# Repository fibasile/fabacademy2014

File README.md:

# FabAcademy 2014 website

In order to be able to build the site or serve it dynamically you will need the following:

- Node.js 10.0.*
- harp.js

You can grab node.js from the [nodejs.org](http://nodejs.org) website, and install a binary package for your platform.

Once this is done just type:

	> npm install -g harp

Then clone this repository and run:

	> harp server

this will start a webserver on your localhost:9000 port with the complete website.

If you want a static version, you can run in the same folder:

	> harp compile

This will create a www folder containing the static website.

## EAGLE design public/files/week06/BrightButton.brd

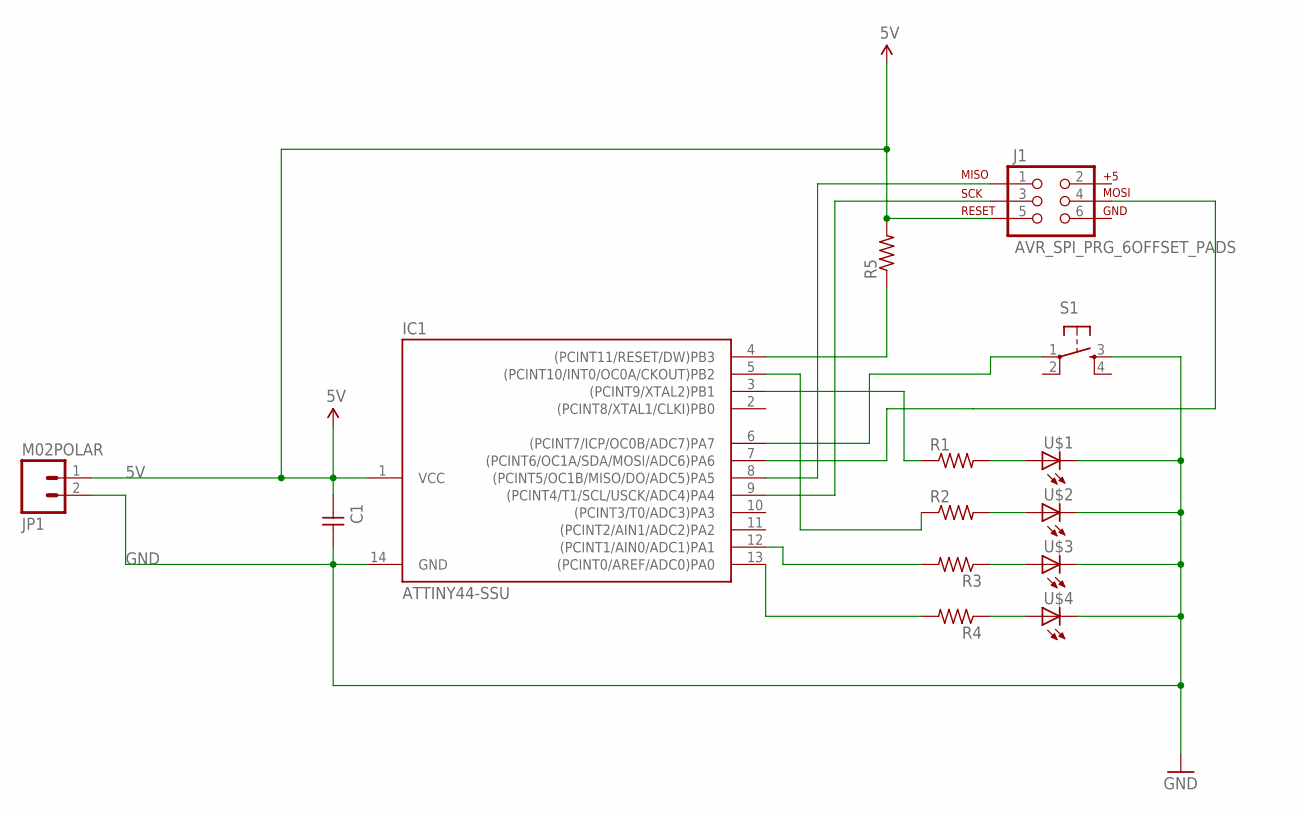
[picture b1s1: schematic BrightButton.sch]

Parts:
C1: UNPOLARIZED_CAPACITOR1206; 1206
IC1: ATTINY44-SSU; SOIC14
J1: AVR_SPI_PRG_6OFFSET_PADS; 2X3_OFFSET
JP1: M02POLAR; MOLEX-1X2
R1, R2, R3, R4, R5: RESISTOR1206; 1206
S1: 6MM_SWITCH6MM_SWITCH; 6MM_SWITCH
U$1, U$2, U$3, U$4: LED1206; 1206

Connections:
5V: C1.1, IC1.1 (VCC), J1.5, JP1.1, R5.2
GND: C1.2, IC1.14 (GND), JP1.2, S1.3 (S), U$1.2 (C), U$2.2 (C), U$3.2 (C), U$4.2 (C)
unnamed: R3.1, U$3.1 (A)
unnamed: IC1.12 ((PCINT1/AIN0/ADC1)PA1), R3.2
unnamed: R2.2, U$2.1 (A)
unnamed: R4.1, U$4.1 (A)
unnamed: R1.2, U$1.1 (A)
unnamed: IC1.5 ((PCINT10/INT0/OC0A/CKOUT)PB2), R2.1
unnamed: IC1.3 ((PCINT9/XTAL2)PB1), R1.1
unnamed: IC1.13 ((PCINT0/AREF/ADC0)PA0), R4.2
unnamed: IC1.4 ((PCINT11/RESET/DW)PB3), R5.1
unnamed: IC1.8 ((PCINT5/OC1B/MISO/DO/ADC5)PA5), J1.1
unnamed: IC1.9 ((PCINT4/T1/SCL/USCK/ADC4)PA4), J1.3
unnamed: IC1.7 ((PCINT6/OC1A/SDA/MOSI/ADC6)PA6), J1.4
unnamed: IC1.6 ((PCINT7/ICP/OC0B/ADC7)PA7), S1.1

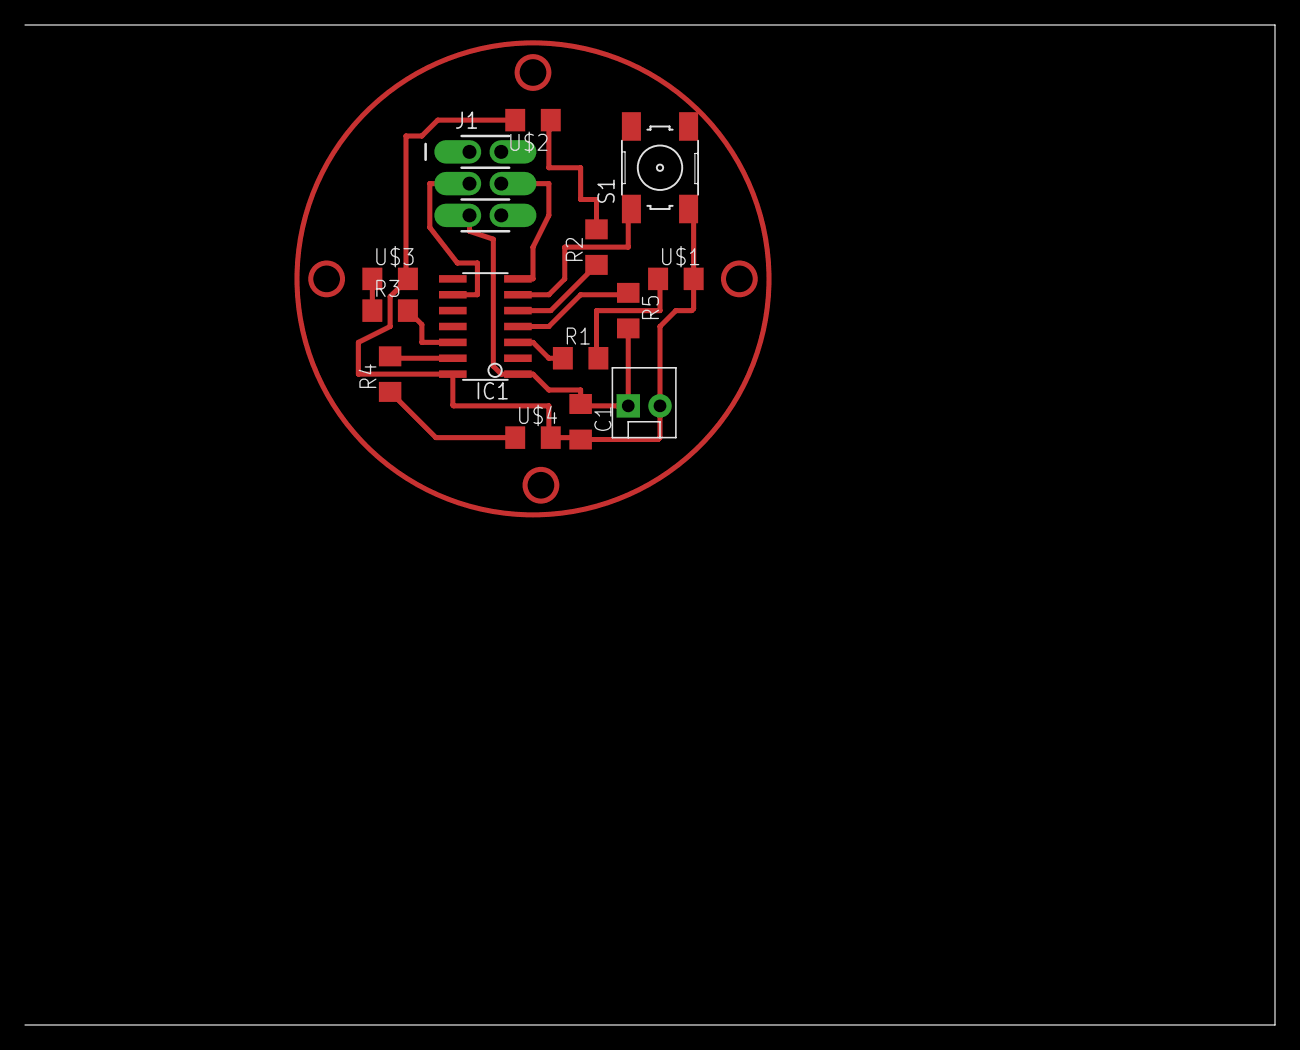
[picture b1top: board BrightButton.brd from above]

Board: 2 copper layers, 100.0 x 80.0 mm, 14 parts (0 on the bottom side), 15 nets.

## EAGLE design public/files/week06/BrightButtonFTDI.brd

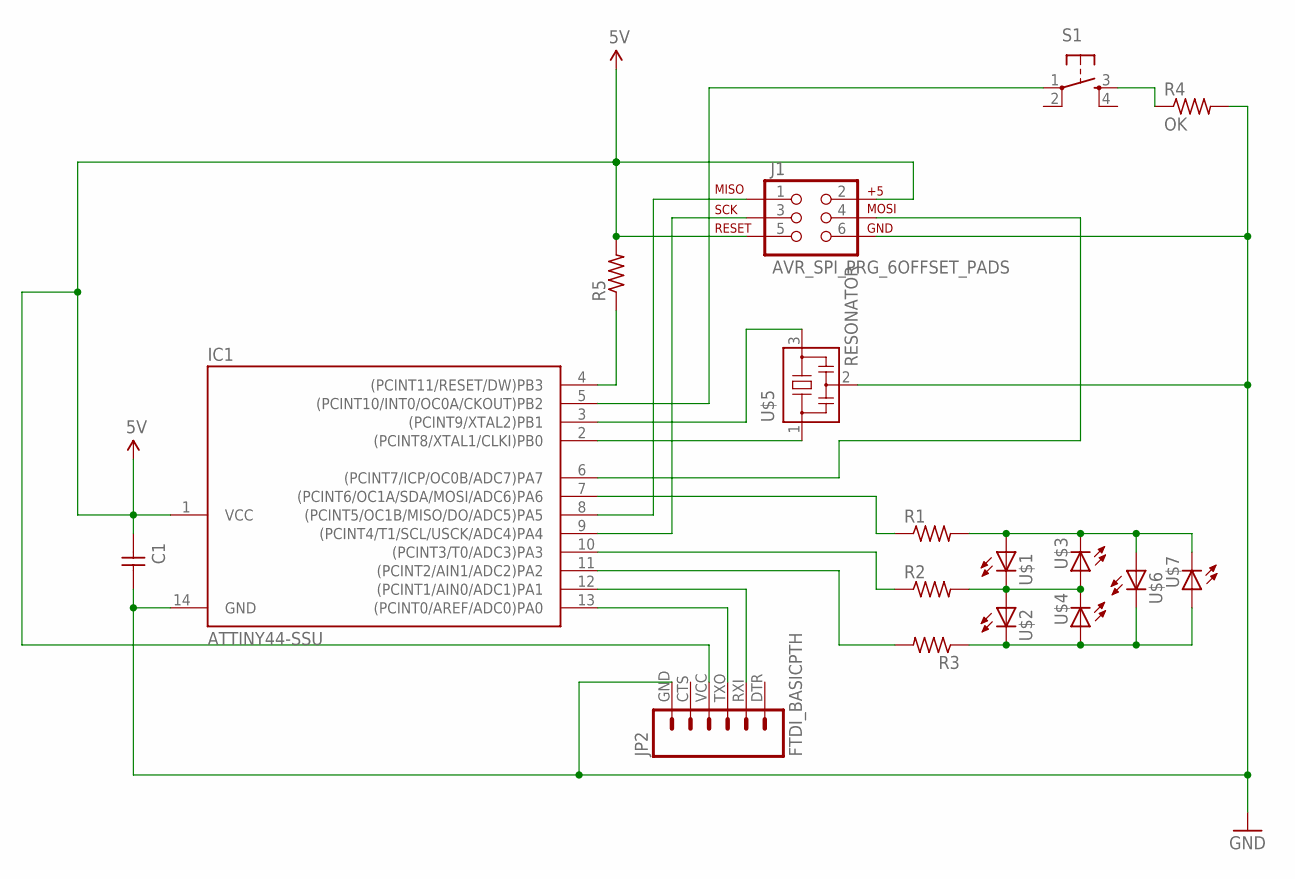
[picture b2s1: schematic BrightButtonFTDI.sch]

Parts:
C1: UNPOLARIZED_CAPACITOR1206; 1206
IC1: ATTINY44-SSU; SOIC14
J1: AVR_SPI_PRG_6OFFSET_PADS; 2X3_OFFSET
JP2: FTDI_BASICPTH; FTDI_BASIC
R1, R2, R3, R5: RESISTOR1206; 1206
R4: OK; 1206
S1: 6MM_SWITCH6MM_SWITCH; 6MM_SWITCH
U$1, U$2, U$3, U$4, U$6, U$7: LED1206; 1206
U$5: RESONATOR; EFOBM

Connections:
5V: C1.1, IC1.1 (VCC), J1.2, J1.5, JP2.VCC (4), R5.2
GND: C1.2, IC1.14 (GND), JP2.GND (6), R4.2, U$5.2
unnamed: R2.2, U$1.2 (C), U$2.1 (A), U$3.1 (A), U$4.2 (C)
unnamed: IC1.13 ((PCINT0/AREF/ADC0)PA0), JP2.TXO (3)
unnamed: R1.2, U$1.1 (A), U$3.2 (C), U$6.1 (A), U$7.2 (C)
unnamed: R3.1, U$2.2 (C), U$4.1 (A), U$6.2 (C), U$7.1 (A)
unnamed: R4.1, S1.3 (S)
unnamed: IC1.12 ((PCINT1/AIN0/ADC1)PA1), JP2.RXI (2)
unnamed: IC1.2 ((PCINT8/XTAL1/CLKI)PB0), U$5.1
unnamed: IC1.3 ((PCINT9/XTAL2)PB1), U$5.3
unnamed: IC1.4 ((PCINT11/RESET/DW)PB3), R5.1
unnamed: IC1.8 ((PCINT5/OC1B/MISO/DO/ADC5)PA5), J1.1
unnamed: IC1.9 ((PCINT4/T1/SCL/USCK/ADC4)PA4), J1.3
unnamed: IC1.6 ((PCINT7/ICP/OC0B/ADC7)PA7), J1.4
unnamed: IC1.5 ((PCINT10/INT0/OC0A/CKOUT)PB2), S1.1
unnamed: IC1.7 ((PCINT6/OC1A/SDA/MOSI/ADC6)PA6), R1.1
unnamed: IC1.10 ((PCINT3/T0/ADC3)PA3), R2.1
unnamed: IC1.11 ((PCINT2/AIN1/ADC2)PA2), R3.2

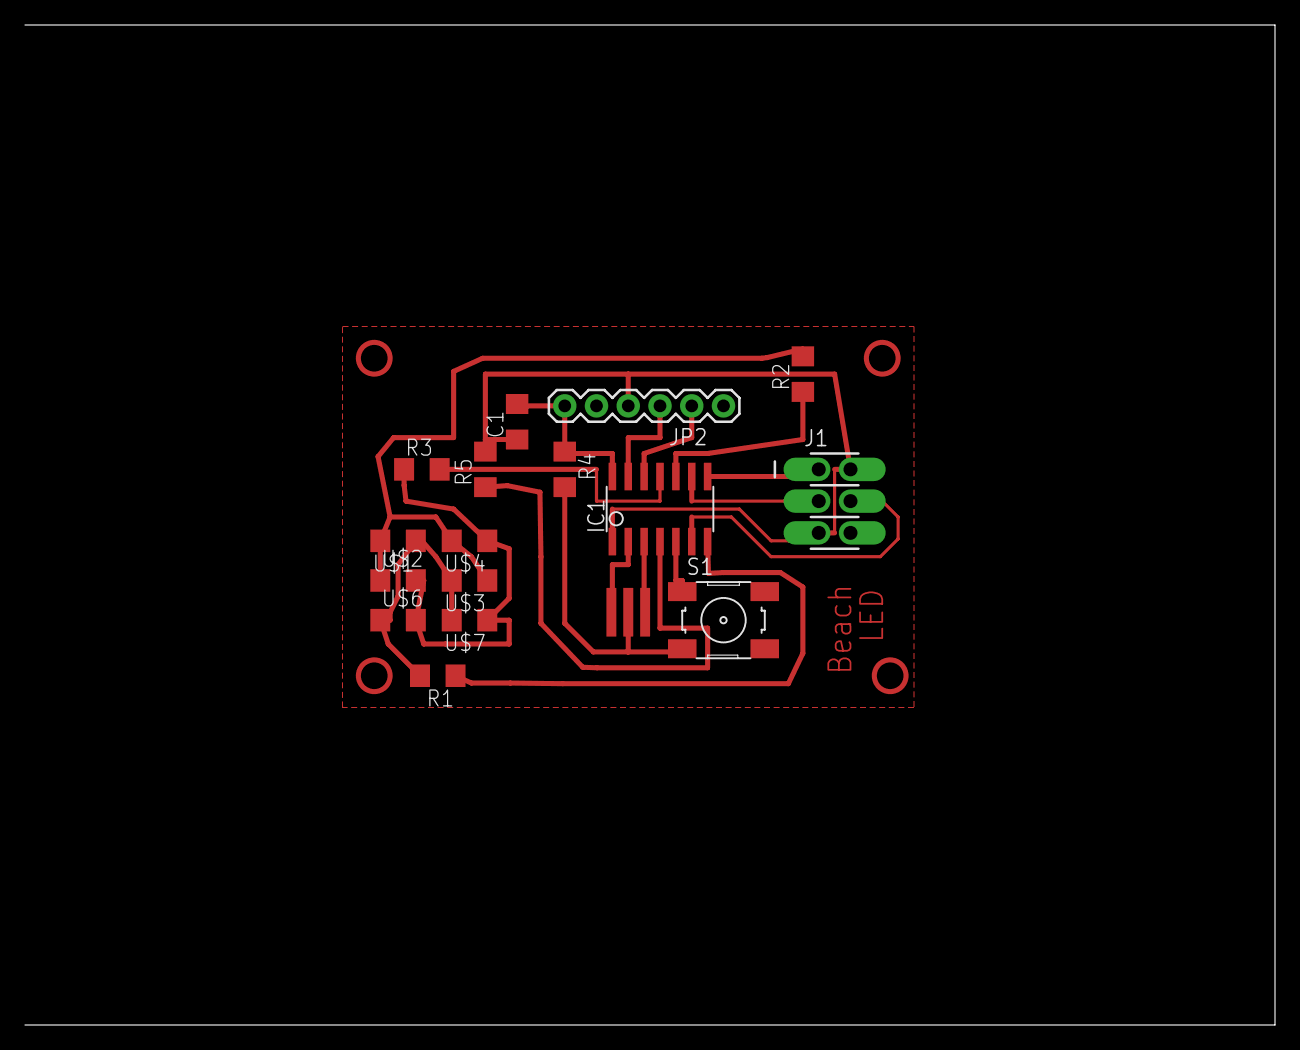
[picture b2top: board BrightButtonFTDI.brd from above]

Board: 2 copper layers, 100.0 x 80.0 mm, 17 parts (0 on the bottom side), 18 nets.

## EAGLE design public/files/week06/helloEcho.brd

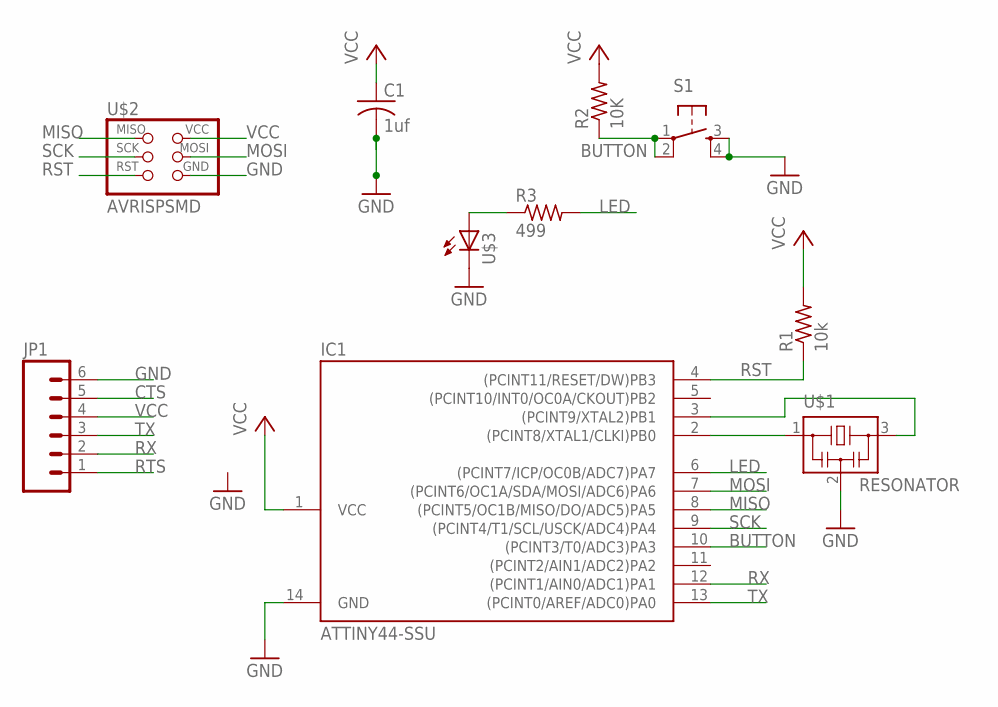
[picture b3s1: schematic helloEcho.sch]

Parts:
C1: 1uf; C1206
IC1: ATTINY44-SSU; SOIC14
JP1: M06SMD; 1X06-SMD
R1: 10k; R1206
R2: 10K; 1206
R3: 499; 1206
S1: 6MM_SWITCH6MM_SWITCH; 6MM_SWITCH
U$1: RESONATOR; EFOBM
U$2: AVRISPSMD; 2X03SMD
U$3: LED1206; 1206

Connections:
BUTTON: IC1.10 ((PCINT3/T0/ADC3)PA3), R2.1, S1.1, S1.2 (P1)
CTS: JP1.5
GND: C1.2, IC1.14 (GND), JP1.6, S1.3 (S), S1.4 (S1), U$1.2, U$2.6 (GND), U$3.2 (C)
LED: IC1.6 ((PCINT7/ICP/OC0B/ADC7)PA7), R3.2
MISO: IC1.8 ((PCINT5/OC1B/MISO/DO/ADC5)PA5), U$2.1 (MISO)
MOSI: IC1.7 ((PCINT6/OC1A/SDA/MOSI/ADC6)PA6), U$2.4 (MOSI)
unnamed: IC1.2 ((PCINT8/XTAL1/CLKI)PB0), U$1.1
unnamed: IC1.3 ((PCINT9/XTAL2)PB1), U$1.3
unnamed: R3.1, U$3.1 (A)
RST: IC1.4 ((PCINT11/RESET/DW)PB3), R1.1, U$2.5 (RST)
RTS: JP1.1
RX: IC1.12 ((PCINT1/AIN0/ADC1)PA1), JP1.2
SCK: IC1.9 ((PCINT4/T1/SCL/USCK/ADC4)PA4), U$2.3 (SCK)
TX: IC1.13 ((PCINT0/AREF/ADC0)PA0), JP1.3
VCC: C1.1, IC1.1 (VCC), JP1.4, R1.2, R2.2, U$2.2 (VCC)

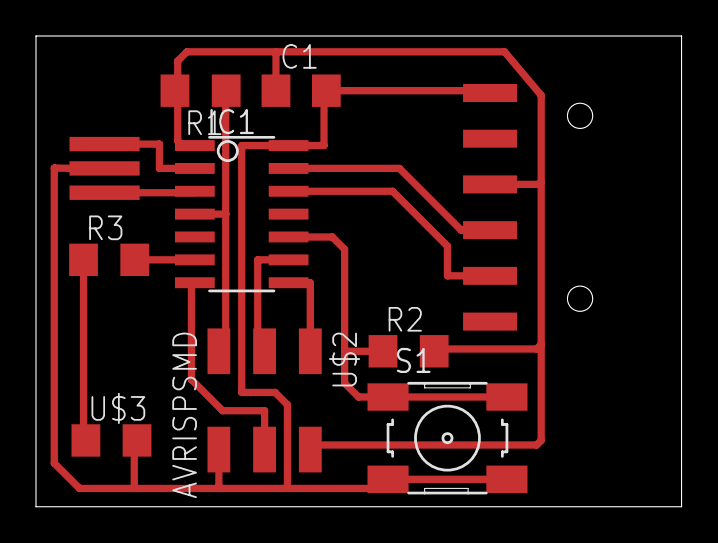
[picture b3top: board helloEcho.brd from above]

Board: 1 copper layer, 35.9 x 26.2 mm, 10 parts (0 on the bottom side), 13 nets.

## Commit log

2014-01-30 initial import
2014-01-30 Added readme
2014-01-30 added project description
2014-02-03 update website
2014-02-11 update for week 2
2014-02-18 update for week 03
2014-03-02 update for week 04
2014-04-01 week 9 update

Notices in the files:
parts and their libraries:
SparkFun-Connectors: Licensing: CC v3.0 Share-Alike You are welcome to use this library for commercial purposes.
